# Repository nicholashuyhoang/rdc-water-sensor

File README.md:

# WaterSensor
Water sensor PCB design project.

Given: 5V Source
Want: 1'x 1' Water Sensor
Constraints: Vout to have a maximum of 3.3V for analog read in, Minimize current draw to be on the magnitude of 1mA

Use N23904 NPN transistor for low current and high robustness. Open schematic for reference.

Calculations
--------------------------------------------------------------------------------------------------------------------------
Assume forward active region:

If we want Vout to have a maximum of 3.3V and we want to minimize current draw to be on the magnitude of 1mA

R2 = 3.3V/1mA = 3.3k ohm 

Ie = 1mA

From testing 2N3904 (did not know the company that made the provided transistor): For Ic = 1mA @ 25 deg celsius, hfe or betaforward current gain is 300.

Ib = Ie/300 = 3.333micro A

We know that Ie = Ic+Ib so Ic = 299/300Ie. They are roughly equal. From testing 2N3904: For Ic = 1mA @ 25 deg celsius, Vbe = 0.67 V.

Vs-(R2*Ib)-Vbe <= Vout ----> 5V-(R2*3.333micro A)-0.67V <= 3.3V

R2 >= 309.03k ohm ---> R2 = 330k ohm

Discussion
--------------------------------------------------------------------------------------------------------------------------
The water sensor is designed with maximum sensitivity in mind. Per competition requirements: Need to detect a 20mL hit but points are awarded for detection of smaller mL hits.

Sensitivity can be decreased by increasing the spacing between the power lines and the copper fill connected to the base of the transistor. 
Additionally, every other power line can be removed to decrease sensitivity.

One potential issue with such a high level of sensitivity is that there is the possibility of a near hit miss balloon that is able to splatter up and over the board onto the sensor.
A mitigation technique for this issue is to erect walls on the border of the marker to prevent ground splash onto the sensor.

Another potential issue is the usage of deionized water. This design works by causing a "short" between two terminals.
A mitigiation technique for this issue is to place a layer of fine grain salt on the board. Salt itself is not conducting. However, it will provide conductivity when placed inside a medium.

Testing w/o AruCo marker, Vout readings: 1 drop - 2.75V, 2 drop - 2.9V, 3 drop - 2.94V, 4 drop - 2.96, 5 drop - 3V, 6 drop - 3V, 7 drop - 3.03V, 8 drop - 3.06V, 9 drop - 3.07V, 10 drop - 3.08V, 11 drop - 3.09V,  12 drop - 3.11V, Saturated - 3.3V

1mL is roughly 25 drops

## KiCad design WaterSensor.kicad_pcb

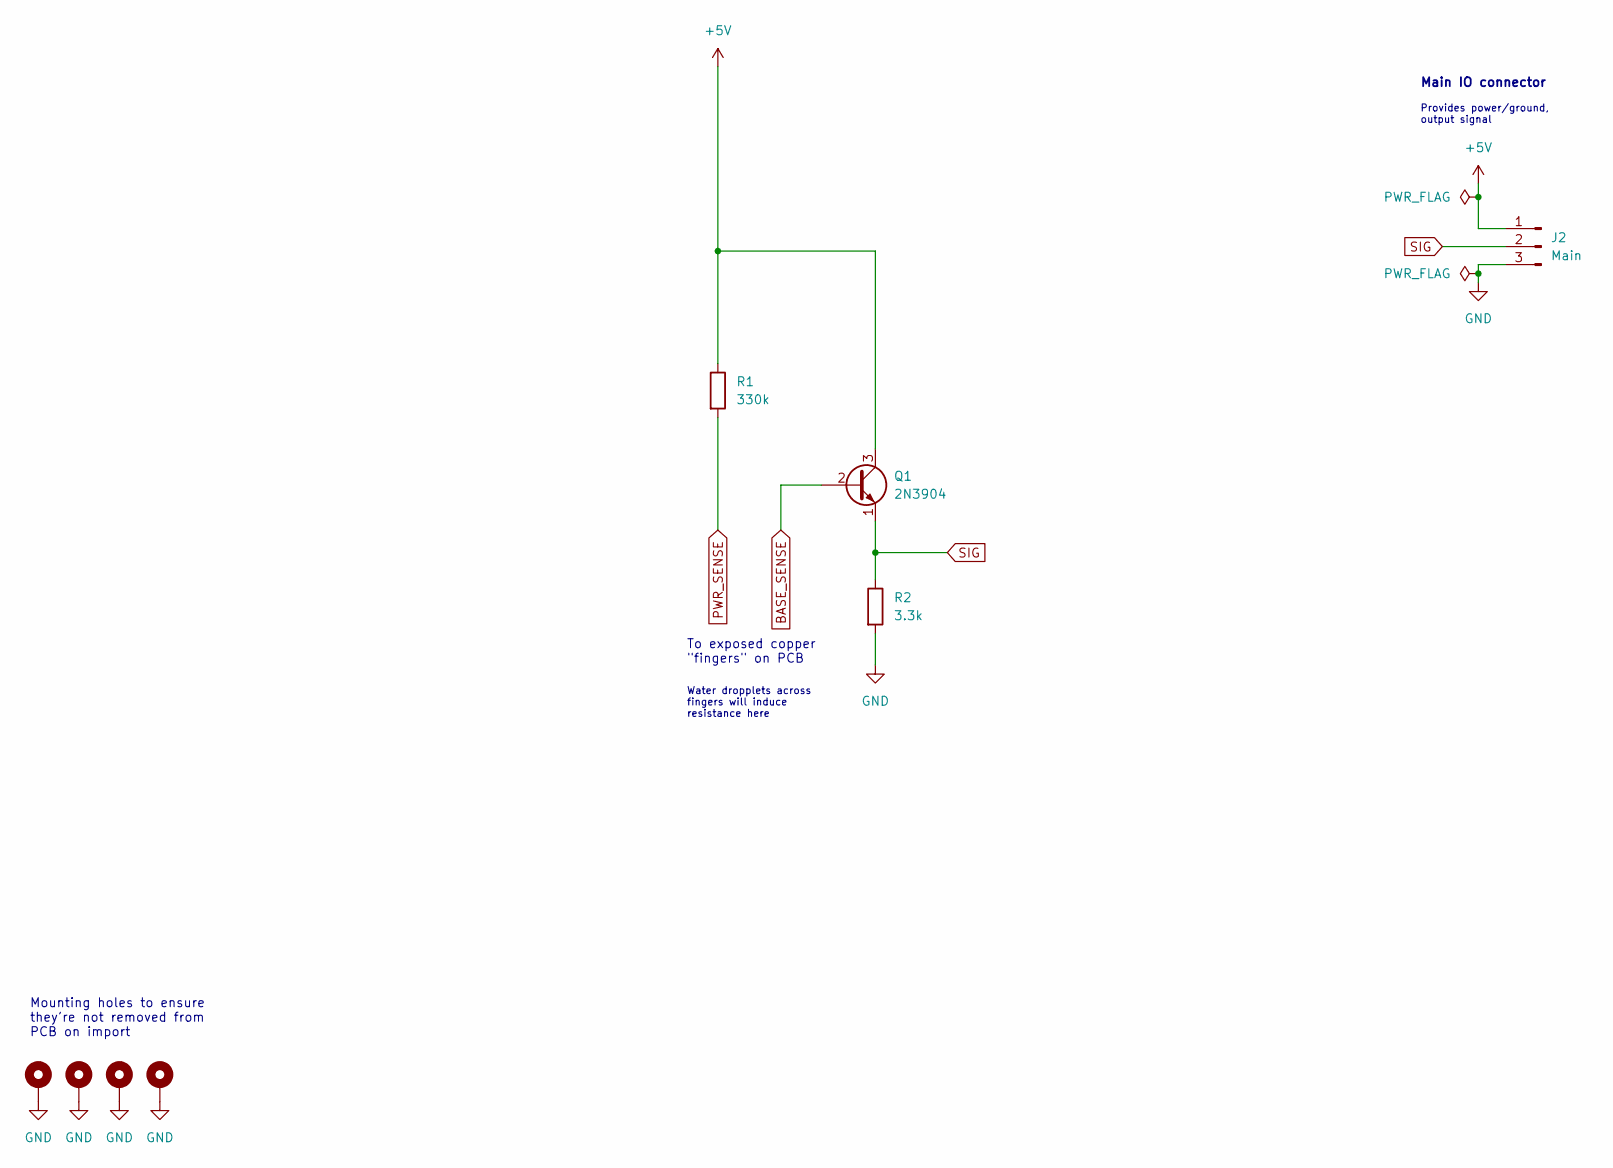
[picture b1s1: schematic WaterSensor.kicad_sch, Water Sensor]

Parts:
H1, H2, H3, H4: MountingHole_Pad; MountingHole_2.5mm_Pad_Via
J2: Main; PinHeader_1x03_P2.54mm_Vertical
Q1: 2N3904; TO-92_Inline
R1: 330k; R_Axial_DIN0204_L3.6mm_D1.6mm_P1.90mm_Vertical
R2: 3.3k; R_Axial_DIN0204_L3.6mm_D1.6mm_P1.90mm_Vertical

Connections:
+5V: J2.1, Q1.3 (C), R1.1
BASE_SENSE: Q1.2 (B)
GND: H1.1, H2.1, H3.1, H4.1, J2.3, R2.2
PWR_SENSE: R1.2
SIG: J2.2, Q1.1 (E), R2.1

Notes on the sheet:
Mounting holes to ensure they're not removed from PCB on import
Water dropplets across fingers will induce resistance here
Provides power/ground, output signal
Main IO connector
To exposed copper "fingers" on PCB

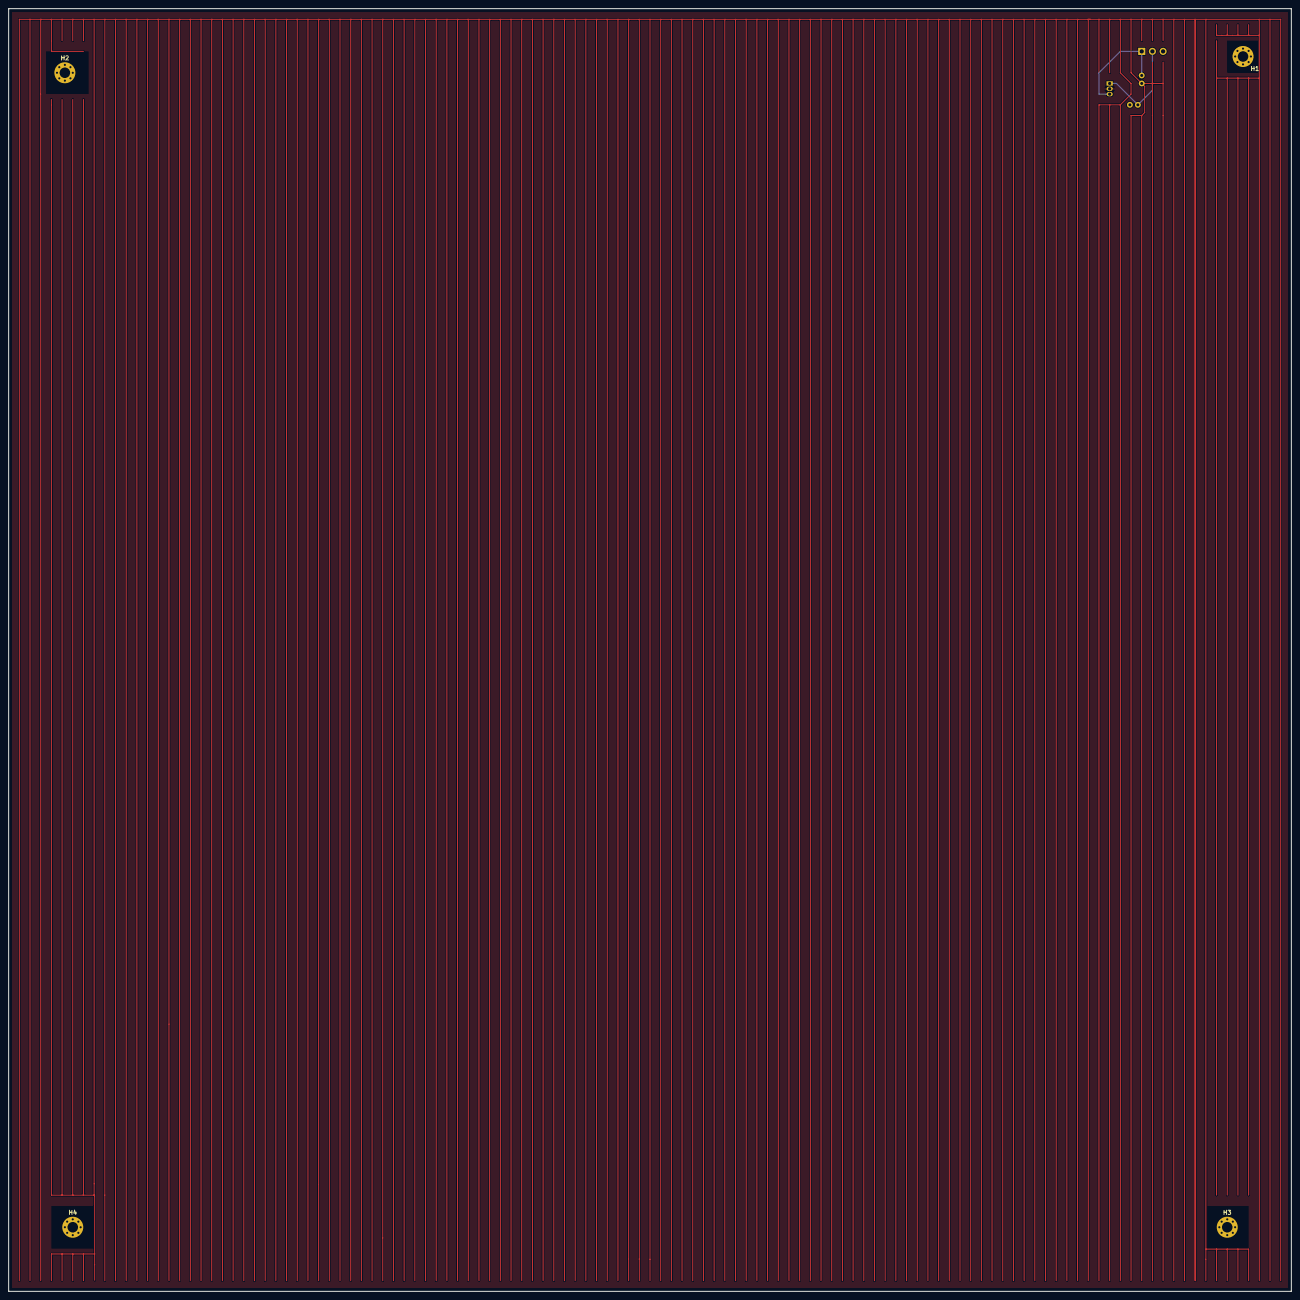
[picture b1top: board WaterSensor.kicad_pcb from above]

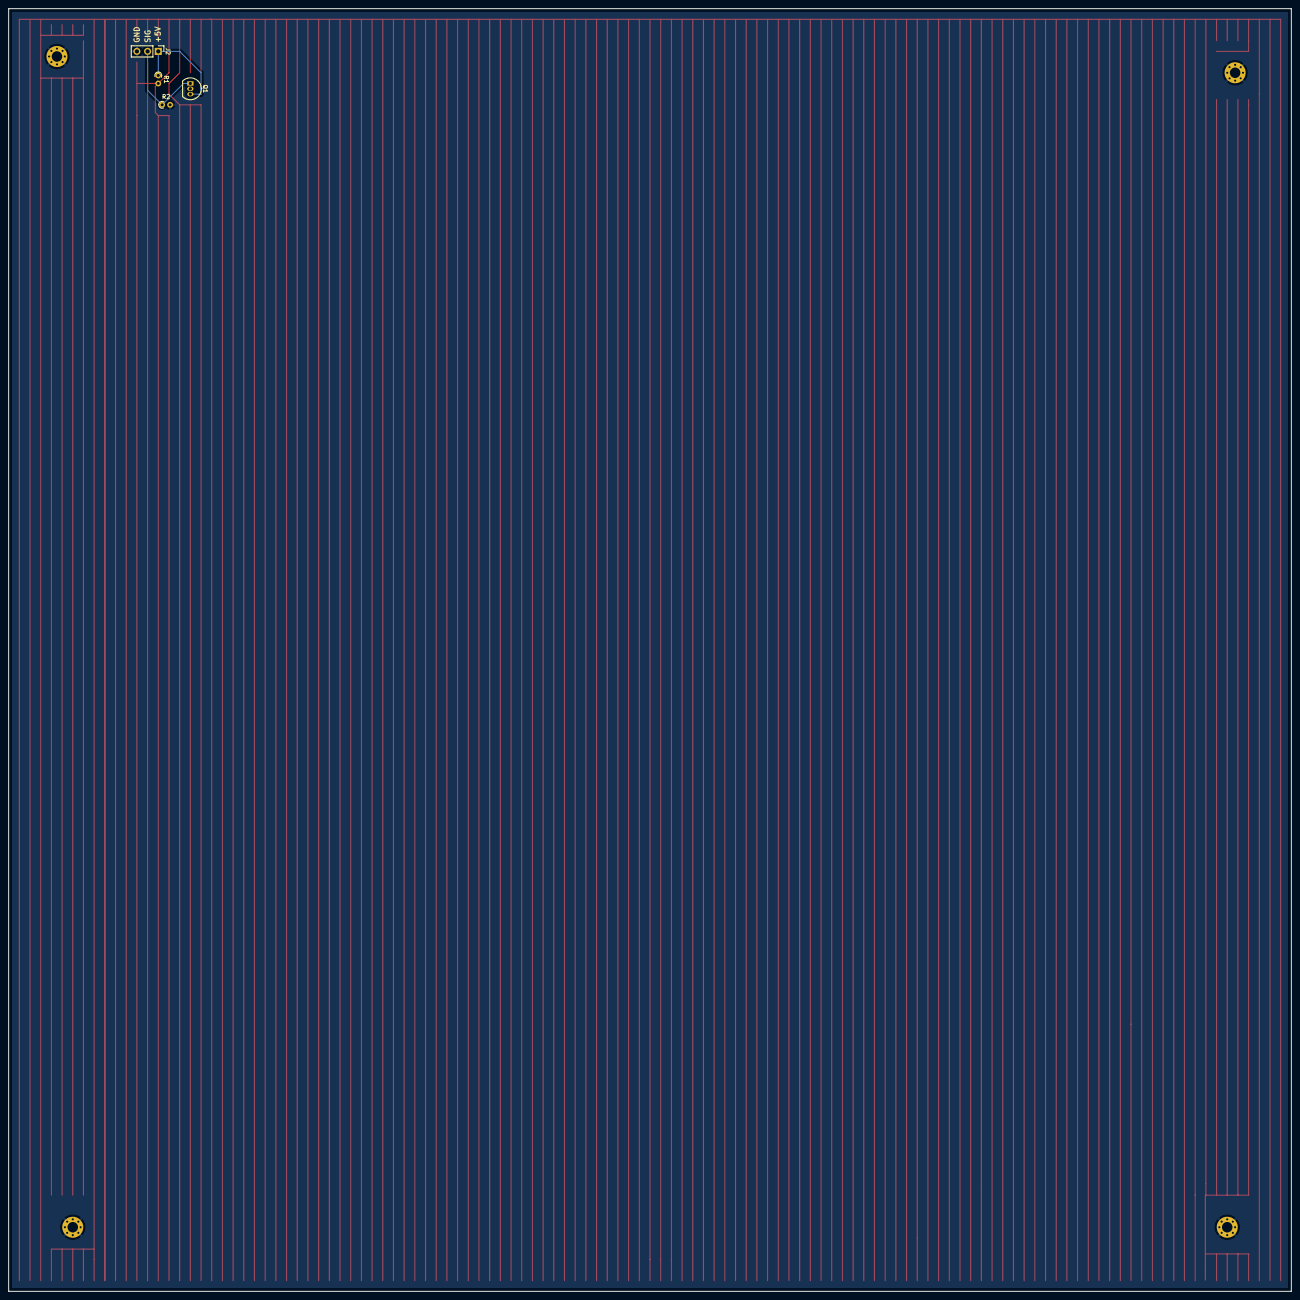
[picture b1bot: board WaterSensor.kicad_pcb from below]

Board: 2 copper layers, 304.8 x 304.8 mm, 8 parts (4 on the bottom side), 3 nets.

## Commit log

2024-02-23 Initial import
2024-02-23 Fixed README
2024-02-23 General cleanup of schematic and PCB
2024-02-24 Change spiral design to finger design
2024-02-25 Removed extra back-side ground plane, added silk screen, added front side mask to expose copper
2024-02-26 Move H1 text outside of copper region
2024-02-26 Update footprints to Kicad 8.0, remove track violation from keepout areas
2024-03-20 Add water sensor SPICE schematic
2024-03-20 Add pulldown resistor and update resistor values to bias a 3.3V output
2024-03-22 Reverse changes as pulldown resistor is not needed
2024-03-22 Update resistor values based on calculations in README
2024-03-22 Update analysis documentation
2024-03-22 Updated testings on sensitivity
